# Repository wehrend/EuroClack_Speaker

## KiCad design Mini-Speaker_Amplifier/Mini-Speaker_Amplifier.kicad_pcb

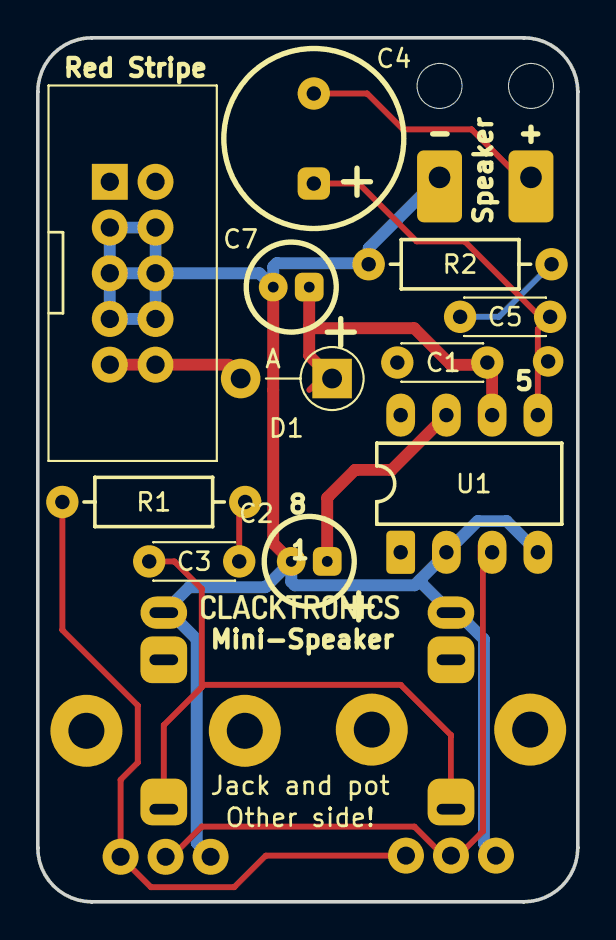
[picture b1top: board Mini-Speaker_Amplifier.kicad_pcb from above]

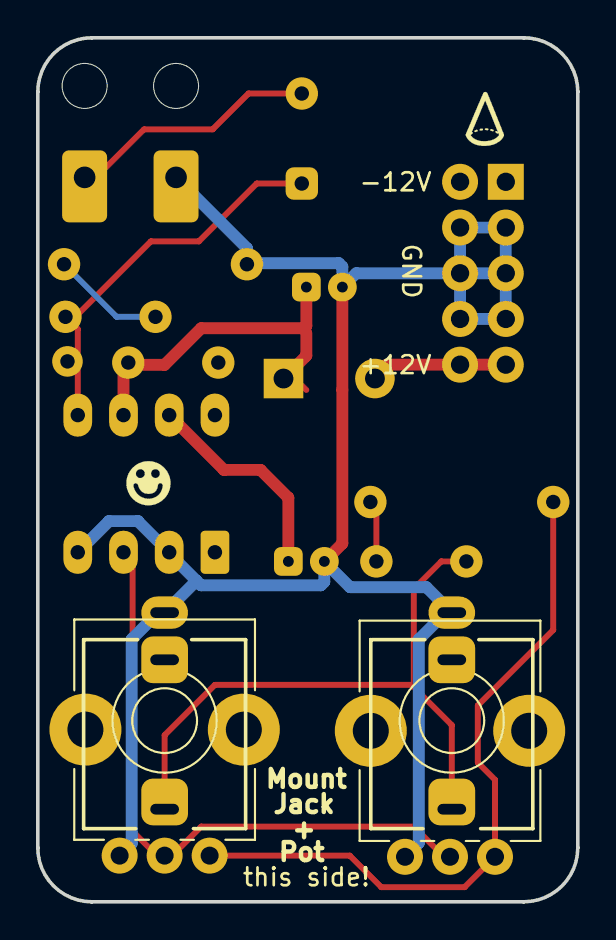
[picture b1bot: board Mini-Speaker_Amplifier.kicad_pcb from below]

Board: 2 copper layers, 30.0 x 48.0 mm, 16 parts (4 on the bottom side), 11 nets.

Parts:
C1, C3, C5: 100nF; C_TH_Disc_P5.00mm
C2, C7: 10μF; C_TH_Elec_5mm_P2mm
C4: 1000μF; C_TH_Elec_10mm_P5mm
D1: 1N5817; D_DO-41_SOD81_P5.08mm_Vertical_AnodeUp
J1, J1#2: AudioJack2; PJ398SM
J2: Conn_02x05; IDC-Header_2x05_P2.54mm_Vertical
LS1: Speaker; Conn_speaker_pads
R1: 470kΩ; R_TH_Axial_250mw_P10.16mm_Horizontal
R2: 10Ω; R_TH_Axial_250mw_P10.16mm_Horizontal
RV1, RV1#2: 10kΩ; POT_TH_Alps_RK09K_Single_Vertical
U1: LM386; DIP-8_W7.62mm

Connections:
+12V: C1.1, C7.1, D1.1, U1.6
GND: C1.2, C2.2, C7.2, J1.S, J1#2.S, J2.3, J2.4, J2.5, J2.6, J2.7, J2.8, LS1.2, R2.1, RV1.3, RV1#2.3, U1.2, U1.4
unnamed: C2.1, U1.7
unnamed: C3.1, R1.2
unnamed: C3.2, J1.T, J1#2.T
unnamed: C4.1, C5.1, U1.5
unnamed: C4.2, LS1.1
unnamed: C5.2, R2.2
unnamed: D1.2, J2.9, J2.10
unnamed: R1.1, RV1.1, RV1#2.1
unnamed: RV1.2, RV1#2.2, U1.3

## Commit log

2024-04-16 Added reverse protection diode Make grid raster 0.5080
